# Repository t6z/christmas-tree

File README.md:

# Christmas Tree

I made a little Christmas tree that lights up and plays a song through a buzzer. I wanted a simple project to expand my skills with schematic capture and PCB layout, and to see how accurate the quick turnaround prototype shops (PCBWAY) do. This project uses an ATTiny402, 3 shift registers to control the LED's, and a simple circuit to try a piezo buzzer. I used Kicad as my EDA tool. It was fun using AI + InkScape to generate different graphics for the tree and import them for the edge cut and silkscreen layers.

## Building Code

### Prereqs

__AVR GNU Toolchain__:

I use the AVR GNU Toolchain (GNU Binutils, GCC, AVR-LibC) to build my code. The attiny402 is supported in the AVR-LibC 2.2.0 release, but ubuntu 24.04 LTS repository only has v2.0.0 (as of December 2024). You could build GNU Binutils, GCC, and AVR-LibC from scratch, but luckily this nice guy already has: [avr-gcc-build](https://github.com/ZakKemble/avr-gcc-build)

I'm using the 14.1.0 (2024-06-14) Release. I downloaded it and extracted it into `~/avr`.

__AVR Dude__:

I downloaded the v8.0 Release of AVR Dude from the [official GitHub repository](https://github.com/avrdudes/avrdude) and extracted it into `~/avr`.

### Building

Run `make`

```bash
$ make
mkdir -p build/src
~/avr/avr-gcc-14.1.0-x64-linux/bin/avr-gcc -c -o build/src/main.o  -std=c11 -Wall -Wextra -Werror -mmcu=attiny402 -DF_CPU=3333333UL -O1 -g -gdwarf-2 -Wl,-Map,build/christmas-tree.map -DDEBUG  src/main.c
mkdir -p build/src
~/avr/avr-gcc-14.1.0-x64-linux/bin/avr-gcc -c -o build/src/notes.o  -std=c11 -Wall -Wextra -Werror -mmcu=attiny402 -DF_CPU=3333333UL -O1 -g -gdwarf-2 -Wl,-Map,build/christmas-tree.map -DDEBUG  src/notes.c
mkdir -p build/src
~/avr/avr-gcc-14.1.0-x64-linux/bin/avr-gcc -c -o build/src/rtttl.o  -std=c11 -Wall -Wextra -Werror -mmcu=attiny402 -DF_CPU=3333333UL -O1 -g -gdwarf-2 -Wl,-Map,build/christmas-tree.map -DDEBUG  src/rtttl.c
mkdir -p build/src
~/avr/avr-gcc-14.1.0-x64-linux/bin/avr-gcc -c -o build/src/tunes.o  -std=c11 -Wall -Wextra -Werror -mmcu=attiny402 -DF_CPU=3333333UL -O1 -g -gdwarf-2 -Wl,-Map,build/christmas-tree.map -DDEBUG  src/tunes.c
~/avr/avr-gcc-14.1.0-x64-linux/bin/avr-gcc -o build/christmas-tree.elf build/src/main.o build/src/notes.o build/src/rtttl.o build/src/tunes.o  -std=c11 -Wall -Wextra -Werror -mmcu=attiny402 -DF_CPU=3333333UL -O1 -g -gdwarf-2 -Wl,-Map,build/christmas-tree.map -DDEBUG 
~/avr/avr-gcc-14.1.0-x64-linux/bin/avr-objdump -h -S build/christmas-tree.elf > build/christmas-tree.lst
~/avr/avr-gcc-14.1.0-x64-linux/bin/avr-size build/christmas-tree.elf
   text	  data	   bss	   dec	   hex	filename
   3586	   156	    44	  3786	   eca	build/christmas-tree.elf
~/avr/avr-gcc-14.1.0-x64-linux/bin/avr-objcopy -j .text -j .data -O ihex build/christmas-tree.elf build/christmas-tree.hex
~/avr/avr-gcc-14.1.0-x64-linux/bin/avr-objcopy -j .text -j .data -O binary build/christmas-tree.elf build/christmas-tree.bin
```

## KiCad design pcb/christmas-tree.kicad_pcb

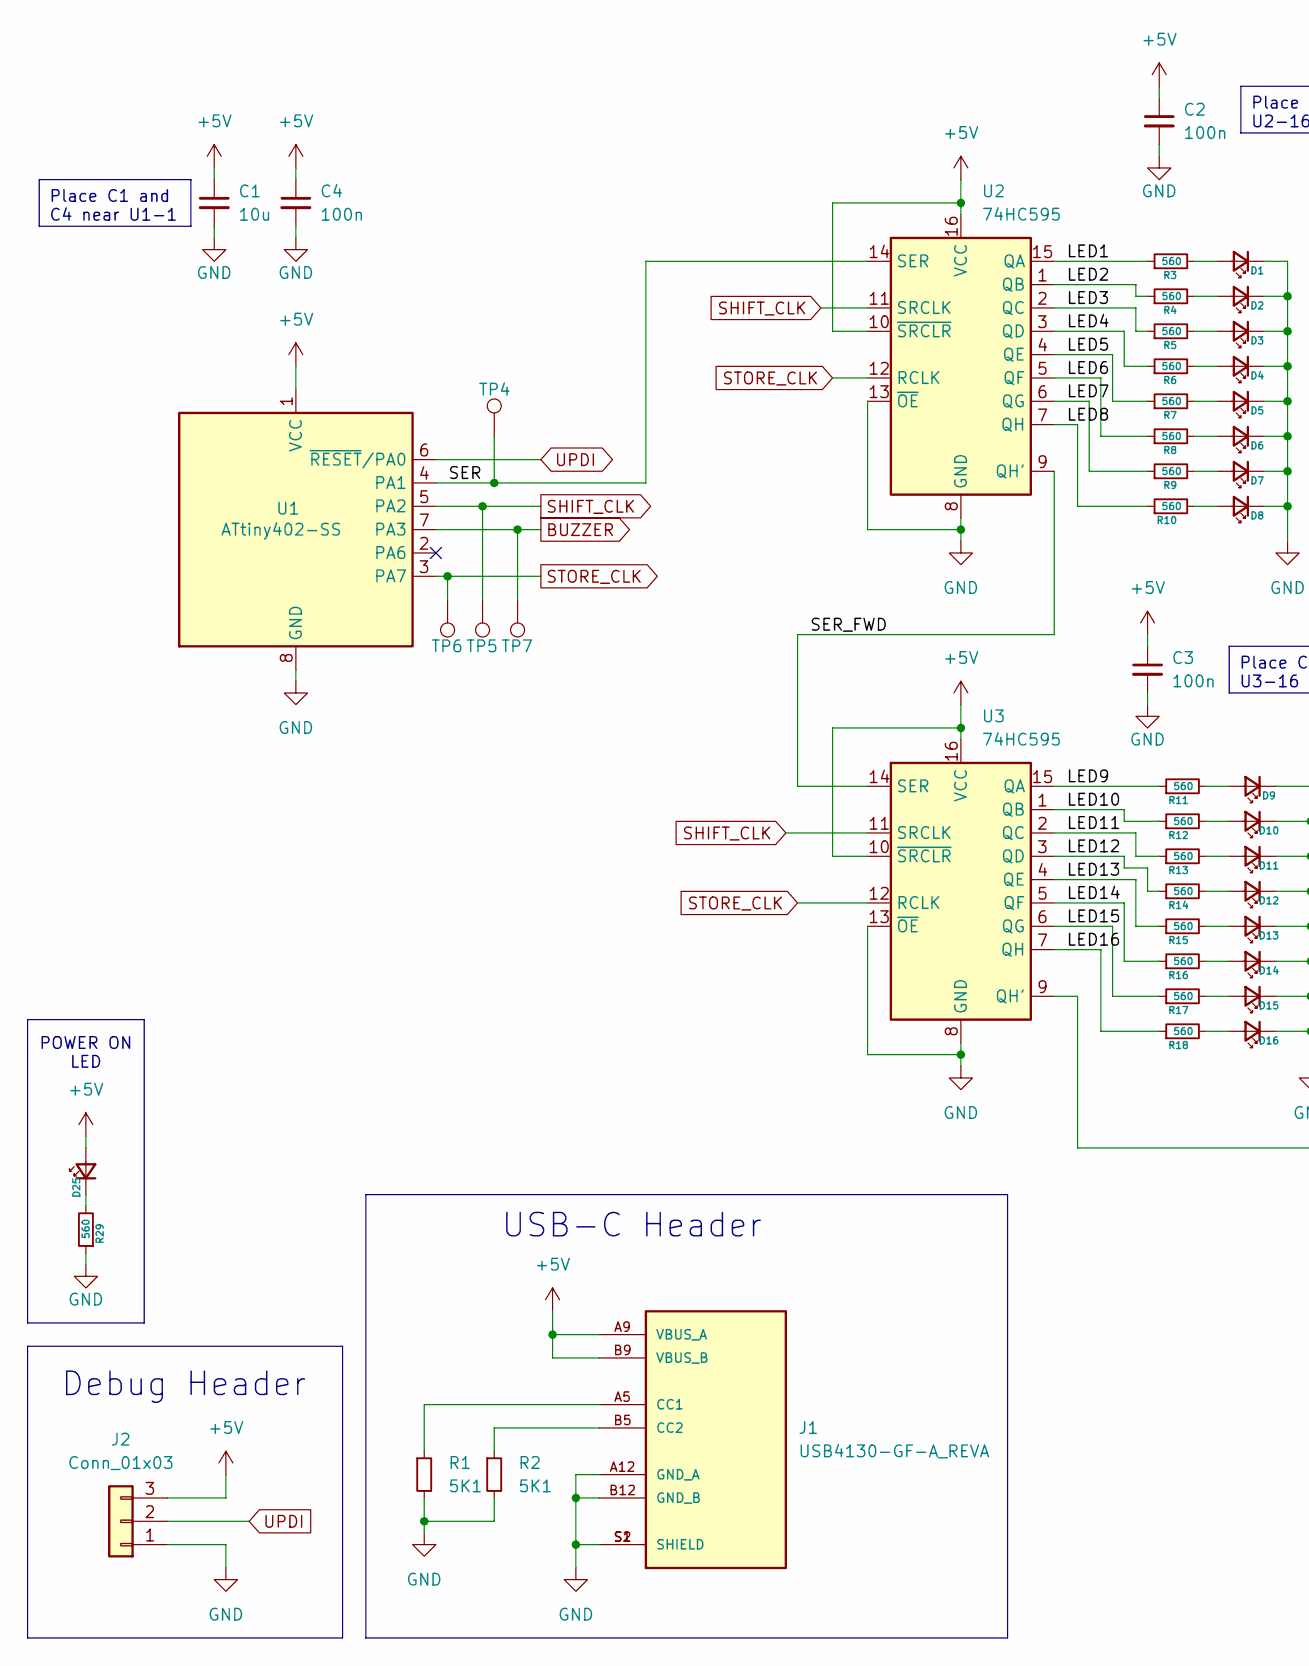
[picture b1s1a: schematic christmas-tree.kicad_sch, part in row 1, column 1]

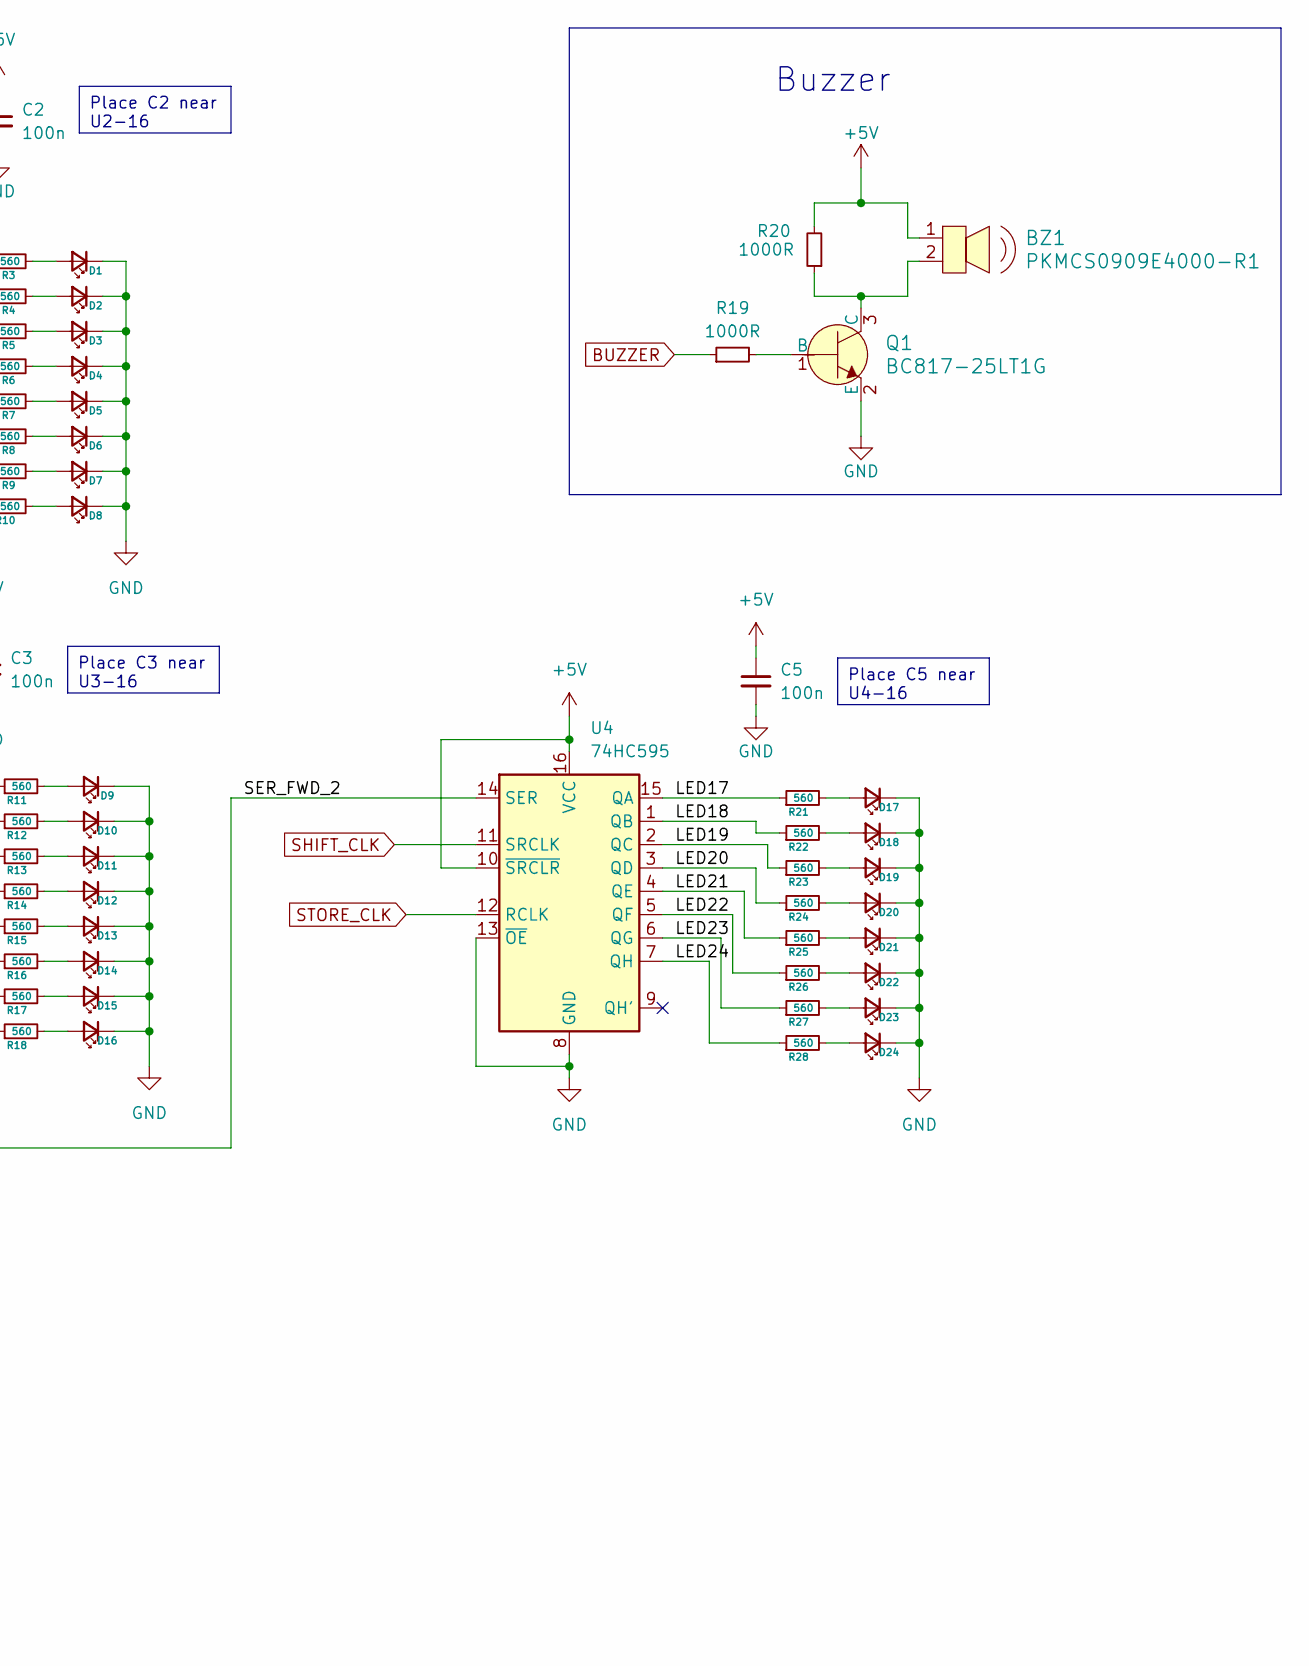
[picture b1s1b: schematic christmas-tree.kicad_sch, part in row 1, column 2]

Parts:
BZ1: PKMCS0909E4000-R1; Piezo_9x9mm_PKMCS0909E4000-R1; MPN PKMCS0909E4000-R1; Digi-Key_PN 490-9647-1-ND
C1: 10u; C_0805_2012Metric_Pad1.18x1.45mm_HandSolder
C2, C3, C4, C5: 100n; C_0805_2012Metric_Pad1.18x1.45mm_HandSolder
D1, D2, D3, D4, D5, D6, D7, D8, D9, D10, D11, D12, D13, D14, D15, D16, D17, D18, D19, D20, D21, D22, D23, D24, D25: LED_Small; LED_0805_2012Metric_Pad1.15x1.40mm_HandSolder
J1: USB4130-GF-A_REVA; GCT_USB4130-GF-A_REVA; PARTREV A
J2: Conn_01x03; PinHeader_1x03_P2.54mm_Vertical
Q1: BC817-25LT1G; SOT-23-3; MPN BC817-25LT1G; Digi-Key_PN BC817-25LT1GOSCT-ND
R1, R2: 5K1; R_0805_2012Metric_Pad1.20x1.40mm_HandSolder
R3, R4, R5, R6, R7, R8, R9, R10, R11, R12, R13, R14, R15, R16, R17, R18, R21, R22, R23, R24, R25, R26, R27, R28, R29: 560; R_0805_2012Metric_Pad1.20x1.40mm_HandSolder
R19, R20: 1000R; R_0805_2012Metric_Pad1.20x1.40mm_HandSolder
TP4: SER; TestPoint_Pad_D1.0mm
TP5: SHIFT_CLK; TestPoint_Pad_D1.0mm
TP6: STORE_CLK; TestPoint_Pad_D1.0mm
TP7: BUZZER; TestPoint_Pad_D1.0mm
U1: ATtiny402-SS; SOIC-8_3.9x4.9mm_P1.27mm
U2, U3, U4: 74HC595; SOIC-16_3.9x9.9mm_P1.27mm

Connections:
+5V: BZ1.1, C1.1, C2.1, C3.1, C4.1, C5.1, D25.2 (A), J1.A9 (VBUS_A), J1.B9 (VBUS_B), J2.3, R20.2, U1.1 (VCC), U2.10 (~SRCLR), U2.16 (VCC), U3.10 (~SRCLR), U3.16 (VCC), U4.10 (~SRCLR), U4.16 (VCC)
/LED1: R3.1, U2.15 (QA)
/LED2: R4.1, U2.1 (QB)
/LED3: R5.1, U2.2 (QC)
/LED4: R6.1, U2.3 (QD)
/LED5: R7.1, U2.4 (QE)
/LED6: R8.1, U2.5 (QF)
/LED7: R9.1, U2.6 (QG)
/LED8: R10.1, U2.7 (QH)
/LED9: R11.1, U3.15 (QA)
/LED10: R12.1, U3.1 (QB)
/LED11: R13.1, U3.2 (QC)
/LED12: R14.1, U3.3 (QD)
/LED13: R15.1, U3.4 (QE)
/LED14: R16.1, U3.5 (QF)
/LED15: R17.1, U3.6 (QG)
/LED16: R18.1, U3.7 (QH)
/LED17: R21.1, U4.15 (QA)
/LED18: R22.1, U4.1 (QB)
/LED19: R23.1, U4.2 (QC)
/LED20: R24.1, U4.3 (QD)
/LED21: R25.1, U4.4 (QE)
/LED22: R26.1, U4.5 (QF)
/LED23: R27.1, U4.6 (QG)
/LED24: R28.1, U4.7 (QH)
/SER: TP4.1, U1.4 (PA1), U2.14 (SER)
/SER_FWD: U2.9 (QH'), U3.14 (SER)
/SER_FWD_2: U3.9 (QH'), U4.14 (SER)
BUZZER: R19.1, TP7.1, U1.7 (PA3)
GND: C1.2, C2.2, C3.2, C4.2, C5.2, D1.1 (K), D2.1 (K), D3.1 (K), D4.1 (K), D5.1 (K), D6.1 (K), D7.1 (K), D8.1 (K), D9.1 (K), D10.1 (K), D11.1 (K), D12.1 (K), D13.1 (K), D14.1 (K), D15.1 (K), D16.1 (K), D17.1 (K), D18.1 (K), D19.1 (K), D20.1 (K), D21.1 (K), D22.1 (K), D23.1 (K), D24.1 (K), J1.A12 (GND_A), J1.B12 (GND_B), J1.S1 (SHIELD), J1.S2 (SHIELD), J2.1, Q1.2 (E), R1.2, R2.2, R29.1, U1.8 (GND), U2.8 (GND), U2.13 (~OE), U3.8 (GND), U3.13 (~OE), U4.8 (GND), U4.13 (~OE)
unnamed: D1.2 (A), R3.2
unnamed: D2.2 (A), R4.2
unnamed: D3.2 (A), R5.2
unnamed: D4.2 (A), R6.2
unnamed: D5.2 (A), R7.2
unnamed: D6.2 (A), R8.2
unnamed: D7.2 (A), R9.2
unnamed: D8.2 (A), R10.2
unnamed: D9.2 (A), R11.2
unnamed: D10.2 (A), R12.2
unnamed: D11.2 (A), R13.2
unnamed: D12.2 (A), R14.2
unnamed: D13.2 (A), R15.2
unnamed: D14.2 (A), R16.2
unnamed: D15.2 (A), R17.2
unnamed: D16.2 (A), R18.2
unnamed: D17.2 (A), R21.2
unnamed: D18.2 (A), R22.2
unnamed: D19.2 (A), R23.2
unnamed: D20.2 (A), R24.2
unnamed: D21.2 (A), R25.2
unnamed: D22.2 (A), R26.2
unnamed: D23.2 (A), R27.2
unnamed: D24.2 (A), R28.2
unnamed: D25.1 (K), R29.2
unnamed: J1.A5 (CC1), R1.1
unnamed: J1.B5 (CC2), R2.1
unnamed: Q1.1 (B), R19.2
unnamed: BZ1.2, Q1.3 (C), R20.1
SHIFT_CLK: TP5.1, U1.5 (PA2), U2.11 (SRCLK), U3.11 (SRCLK), U4.11 (SRCLK)
STORE_CLK: TP6.1, U1.3 (PA7), U2.12 (RCLK), U3.12 (RCLK), U4.12 (RCLK)
UPDI: J2.2, U1.6 (~RESET/PA0)

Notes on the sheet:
Place C1 and C4 near U1-1
Place C3 near U3-16
Place C5 near U4-16
Place C2 near U2-16
POWER ON LED
Debug Header
USB-C Header
Buzzer

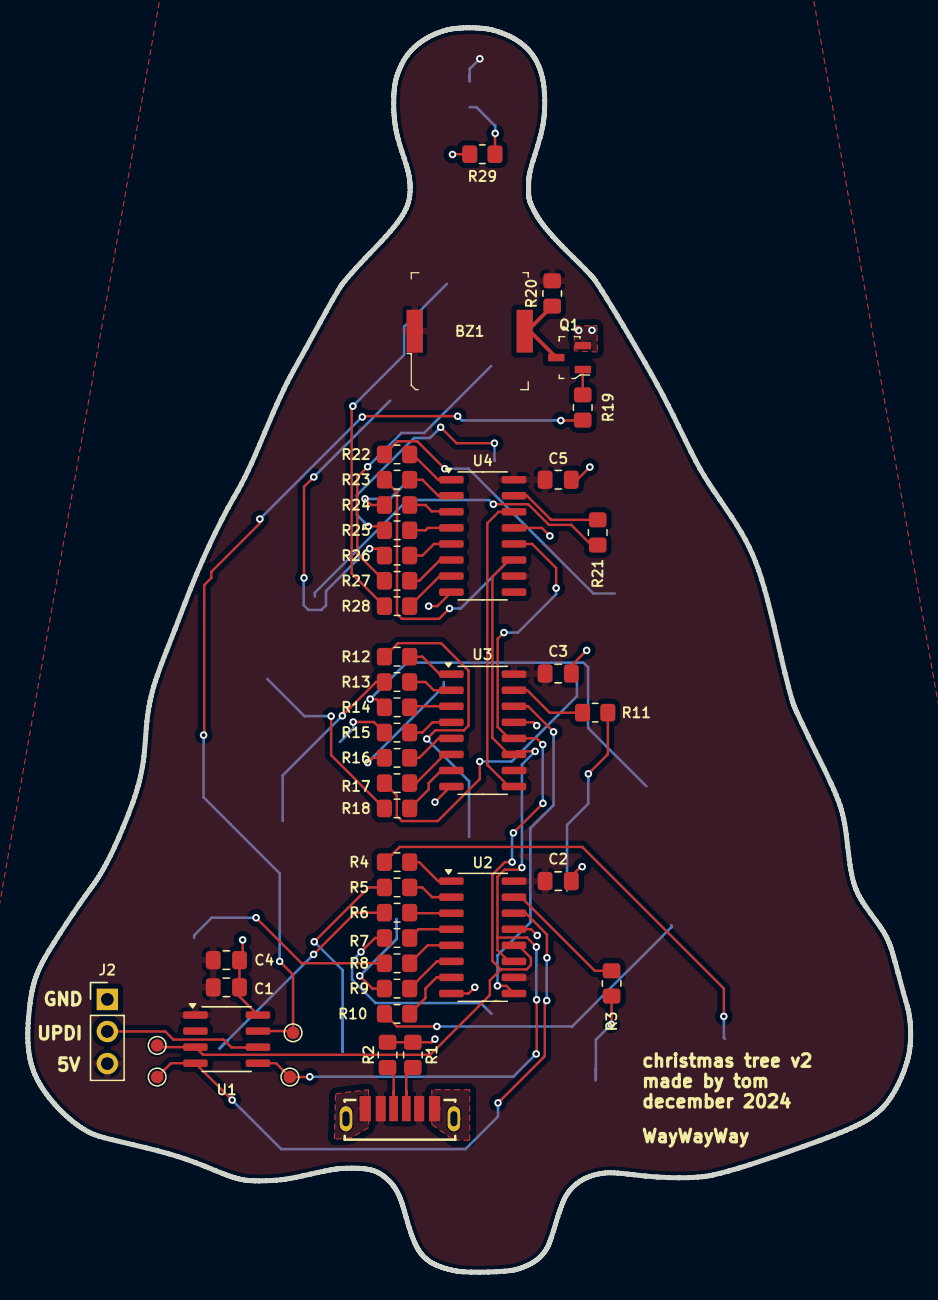
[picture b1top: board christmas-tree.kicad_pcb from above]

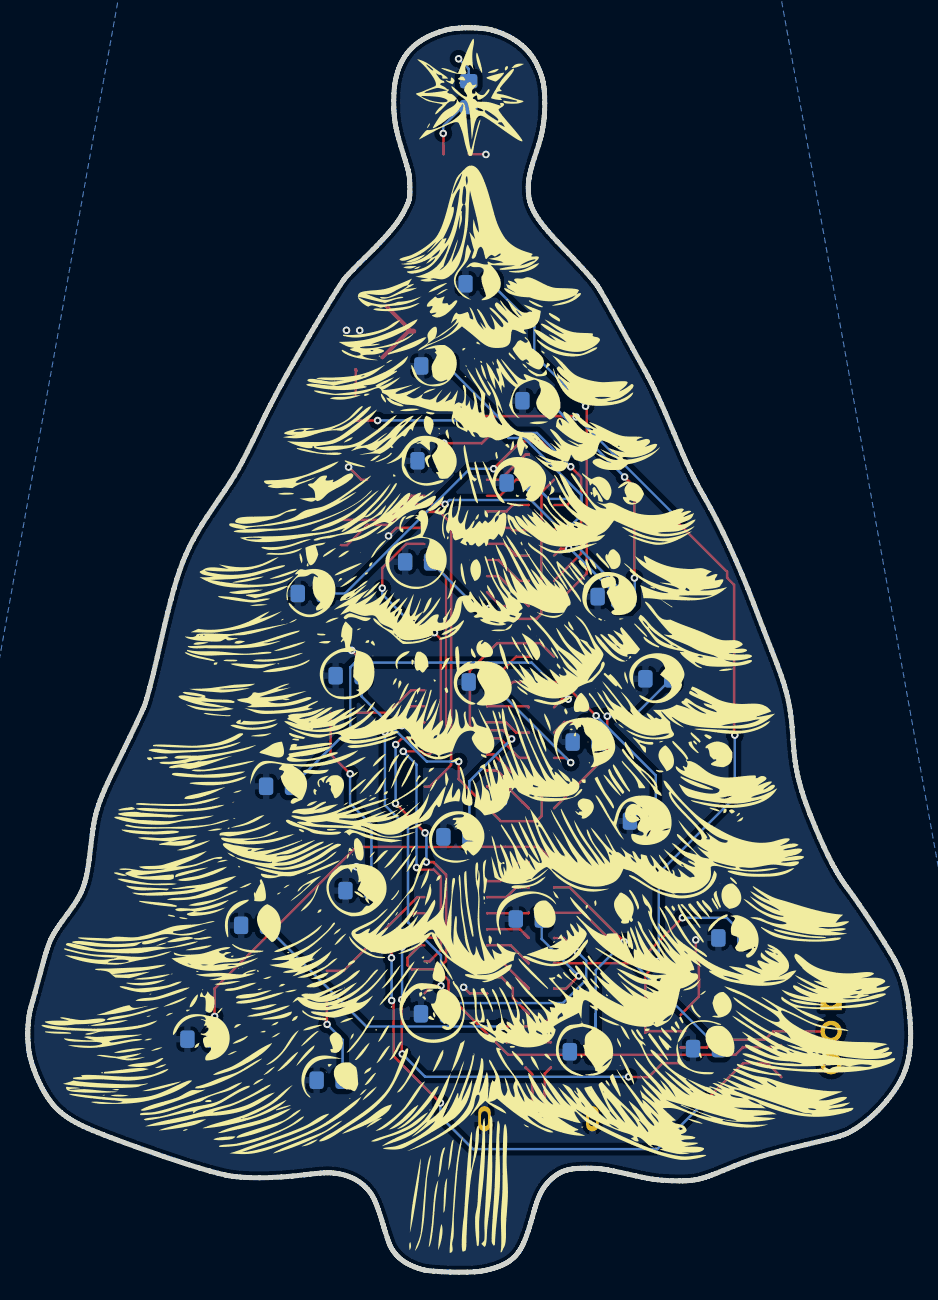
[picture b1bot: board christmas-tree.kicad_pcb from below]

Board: 2 copper layers, 69.8 x 98.4 mm, 71 parts (25 on the bottom side), 62 nets.

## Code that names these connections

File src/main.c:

#include <avr/io.h>
#include <avr/interrupt.h>
#include <util/delay.h>

#include "notes.h"
#include "rtttl.h"
#include "tunes.h"

#define HIGH (1U)
#define LOW  (0U)

#define PIN_SER (1U) /* PA1 */
#define PIN_SHIFT_CLK (2U) /* PA2 */
#define PIN_STORE_CLK (7U) /* PA7 */

#define NUM_LEDS (24U)

Rtttl_Tune_s tune;
volatile Rtttl_Note_s next_note = {
   .d = RTTTL_D1,
   .o = RTTTL_O4,
   .p = RTTTL_PC,
   .s = 0
};
uint16_t cnts_default_note = 0;

uint8_t led_duration[3] = {9,11,13};
uint8_t led_duration_cnt = 0;
uint16_t led_counter = 0;
uint8_t led_turnon[NUM_LEDS] = {0};
uint8_t led_order[NUM_LEDS] = {12, 7, 15, 13, 19, 23, 18, 6, 16, 20, 3, 9, 21, 14, 1, 17, 0, 10, 8, 4, 5, 11, 2, 22};
uint32_t output = 0;
uint8_t counter = 0;

void digitalWrite(uint8_t pin, uint8_t level) {
   if (level) {
      VPORTA_OUT |= (uint8_t)(1U<<pin);
   } else {
      VPORTA_OUT &= (uint8_t)(~(1U<<pin));
   }
}

void shiftOut(uint8_t data)
{
   for (uint8_t i = 0; i < 8; i++)  {
      /* Update serial data pin */
      digitalWrite(PIN_SER, (data & (1 << i)));
      /* Cycle shift clock */
      digitalWrite(PIN_SHIFT_CLK, HIGH);
      digitalWrite(PIN_SHIFT_CLK, LOW);
   }
}

void updateShiftRegister(uint32_t data) {
   /* Set store clock pin low */
   digitalWrite(PIN_STORE_CLK,LOW);

   /* shift upper 8 bits out */
   shiftOut((uint8_t)(data&0xFF));
   shiftOut((uint8_t)((data>>8)&0xFF));
   shiftOut((uint8_t)((data>>16)&0xFF));

   /* Setting store clock pin high again updates shift register's output */
   digitalWrite(PIN_STORE_CLK,HIGH);
}

void update_note (Rtttl_Pitch_e pitch, Rtttl_Octave_e octave) {
   uint16_t period, compare;

   if (pitch == RTTTL_PP) {
      TCA0.SINGLE.CMP0BUF = 0;
   } else {
      if (octave == RTTTL_O4) {
         period = tca0_per[pitch-1];
         compare = tca0_cmp0[pitch-1];
      } else {
         period = tca0_per[pitch-1] >> (octave-4);
         compare = tca0_cmp0[pitch-1] >> (octave-4);
      }
      TCA0.SINGLE.PERBUF = period;
      TCA0.SINGLE.CMP0BUF = compare;
   }
}

void init_clock (void) {
   /* set the 32KHz Oscillator in Run Standby mode so it is on for the RTC */
   CLKCTRL.OSC32KCTRLA = CLKCTRL_RUNSTDBY_bm;
   /* wait for 32KHz Oscillator to be stable */
   while (!((CLKCTRL.MCLKSTATUS&0x10)==0x10));
}

/* Initialize Port */
void init_pins (void) {
   /* GPIO pins are cleared upon RESET */
   /* set PA1,2,3,7 as output pins */
   PORTA.DIR = PIN1_bm | PIN2_bm | PIN3_bm | PIN7_bm;
}

/* Initialize Real Time Clock */
void init_rtc (void) {
   /* select 32KHz clock */
   RTC.CLKSEL = 0;
   /* Set CMP value */
   RTC.CMP = 0xFFFF;
   /* Enable CMP interrupt */
   RTC.INTCTRL = RTC_CMP_bm;
   /* Enable RTC */
   RTC.CTRLA = RTC_RTCEN_bm;
}

/* Initialize Timer A */
void init_tca0 (void) {
   /* Enable CMP0 and set Waveform Generation Mode to Dual-Slope PWM */
   TCA0.SINGLE.CTRLB = TCA_SINGLE_CMP0EN_bm | TCA_SINGLE_WGMODE_DSBOTTOM_gc;

   /* Set Period */
   TCA0.SINGLE.PERBUF = 0x3FFU;
   /* Set CMP0 */
   TCA0.SINGLE.CMP0BUF = 0x1FFU;

   /* Select Clock Divider and Enable Timer */
   TCA0.SINGLE.CTRLA = TCA_SINGLE_CLKSEL_DIV4_gc | TCA_SINGLE_ENABLE_bm;
}

/* Initialize Timer B */
void init_tcb0 (void) {
   TCB0.CCMP = 0xFFF;
   TCB0.INTCTRL = TCB_CAPT_bm;
   TCB0.CTRLA = TCB_CLKSEL_CLKTCA_gc | TCB_ENABLE_bm;
}

void init (void) {
   init_clock();
   init_pins();
   init_rtc();
   init_tca0();
   init_tcb0();
}

void init_tune (char* tune_p) {
   tune.c = 0;
   tune.st = RTTTL_NOERR;
   tune.t = &tune_p[0];
   rtttl_init(&tune);

   cnts_default_note = (uint16_t)((60.0/tune.b)*32768);

   /* if the default length is not a quarter note */
   if (tune.d > RTTTL_D4) {
      cnts_default_note = cnts_default_note * (tune.d/RTTTL_D4);
   } else if (tune.d < RTTTL_D4) {
      cnts_default_note = cnts_default_note * (RTTTL_D4/tune.d);
   }
}

int main (void) {
   uint8_t playing_tune = 0;

   init();
   sei(); /* enable interrupts */

   TCA0.SINGLE.CMP0BUF = 0;

   init_tune((char*)&tune_green[0]);
   next_note = rtttl_next_note(&tune);
   playing_tune = 1;
   /* everything is handled in interrupts */
   /* loop forever */
   for(;;) {
      if (!playing_tune) {
         _delay_ms(5000);
         init_tune((char*)&tune_green[0]);
         next_note = rtttl_next_note(&tune);

         playing_tune = 1;
      } else if (tune.st == RTTTL_DONE){
         playing_tune = 0;
      }
   }

   return 0;
}

ISR(TCB0_INT_vect) {
   if (counter%13==0) {
      led_turnon[led_order[led_counter]] = led_duration[led_duration_cnt];
      led_duration_cnt++;
      if (led_duration_cnt%3==0) led_duration_cnt=0;
      led_counter++;
      if (led_counter%NUM_LEDS==0) led_counter=0;
      output = 0;
      for (uint8_t i = 0; i < NUM_LEDS; i++) {
         if (led_turnon[i]) {
            led_turnon[i]--;
            output |= ((uint32_t)1)<<i;
         }
      }
      updateShiftRegister(output);
   }

   /* update counter */
   counter++;
   if (counter%50==0) counter = 0;
   /* Clear the interrupt flag */
   TCB0.INTFLAGS = TCB_CAPT_bm;
}

ISR(RTC_CNT_vect) {
   uint16_t cnt = RTC.CNT;
   uint16_t cnt_add;

   update_note(next_note.p,next_note.o);

   /* if its the default length */
   if (tune.d == next_note.d) {
      cnt_add = cnts_default_note;
   } else if (((uint8_t)(tune.d/next_note.d)) > 0) {
      cnt_add = (uint16_t)(cnts_default_note * (tune.d/next_note.d));
   } else {cnt_add = (uint16_t)(cnts_default_note / (next_note.d/tune.d));}

   if (next_note.s) {cnt_add += (cnt_add>>1);}

   next_note = rtttl_next_note(&tune);

   RTC.CMP = cnt+cnt_add;
   /* Clear the Compare Match Interrupt Flag */
   RTC.INTFLAGS = RTC_CMP_bm;
}

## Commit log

2025-01-15 finished project
